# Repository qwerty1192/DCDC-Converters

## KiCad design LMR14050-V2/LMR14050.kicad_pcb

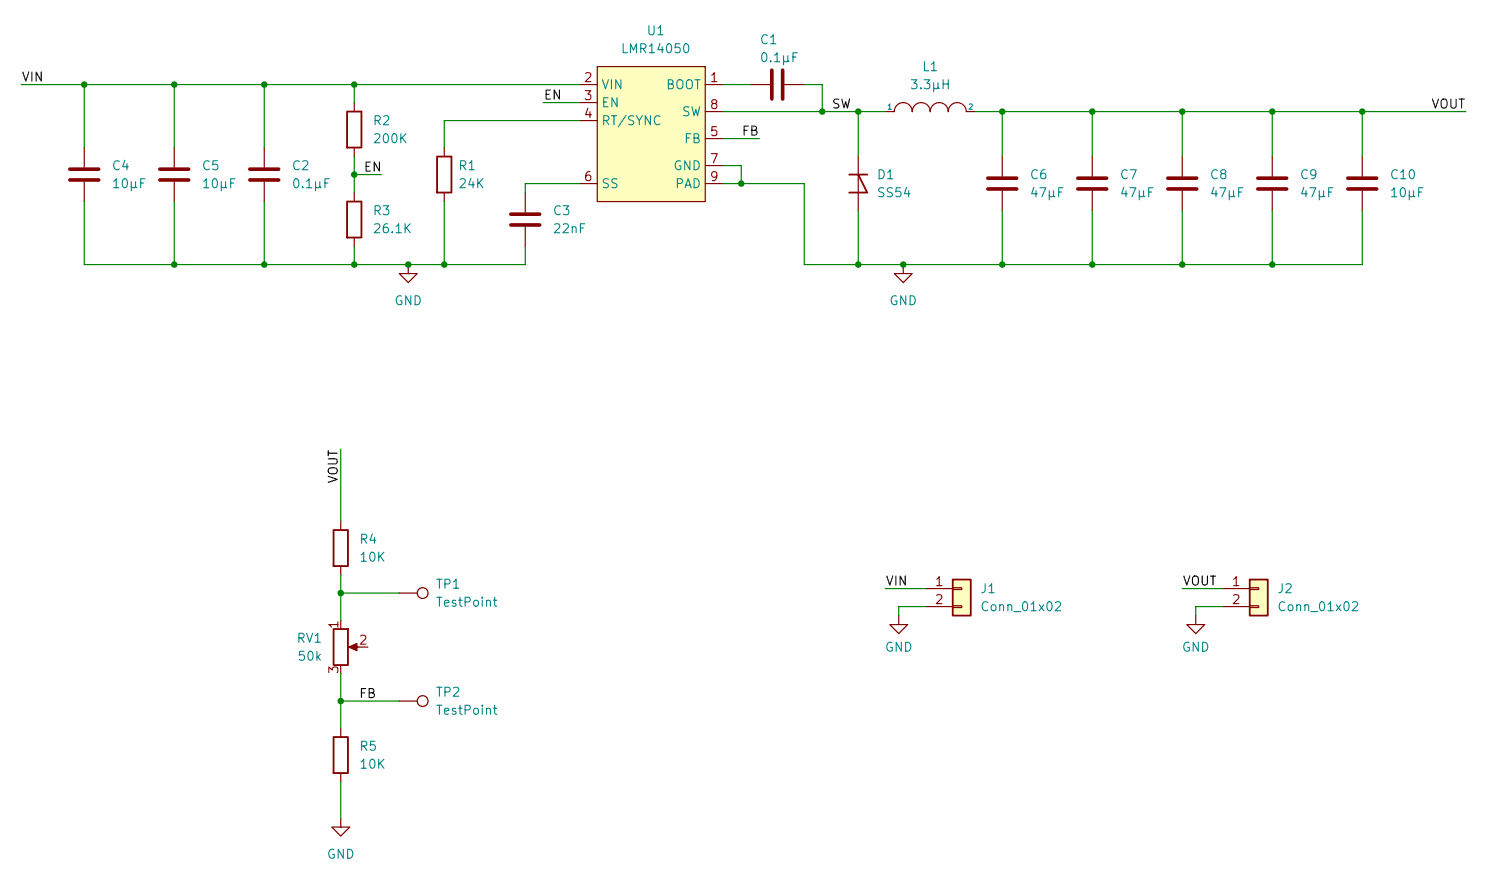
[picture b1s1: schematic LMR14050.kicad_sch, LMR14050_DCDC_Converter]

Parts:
C1, C2: 0.1µF; C_0603_1608Metric
C3: 22nF; C_0603_1608Metric
C4, C5: 10µF; C_1210_3225Metric
C6, C7, C8, C9: 47µF; C_1206_3216Metric
C10: 10µF; C_0603_1608Metric
D1: SS54; D_SMA
J1, J2: Conn_01x02; JST_XH_S2B-XH-A_1x02_P2.50mm_Horizontal
L1: 3.3µH; FX06x0
R1: 24K; R_0603_1608Metric
R2: 200K; R_0603_1608Metric
R3: 26.1K; R_0603_1608Metric
R4, R5: 10K; R_0603_1608Metric
RV1: 50k; G32A
TP1, TP2: TestPoint; TestPoint_Pad_D1.5mm
U1: LMR14050; HSOP-8-1EP_3.9x4.9mm_P1.27mm_EP2.41x3.1mm

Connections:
/EN: R2.2, R3.1, U1.3 (EN)
/FB: R5.1, RV1.3, TP2.1, U1.5 (FB)
/SW: C1.2, D1.1 (K), L1.1, U1.8 (SW)
/VIN: C2.1, C4.1, C5.1, J1.1, R2.1, U1.2 (VIN)
/VOUT: C6.1, C7.1, C8.1, C9.1, C10.1, J2.1, L1.2, R4.1
GND: C2.2, C3.2, C4.2, C5.2, C6.2, C7.2, C8.2, C9.2, C10.2, D1.2 (A), J1.2, J2.2, R1.2, R3.2, R5.2, U1.7 (GND), U1.9 (PAD)
unnamed: R4.2, RV1.1, TP1.1
unnamed: C1.1, U1.1 (BOOT)
unnamed: R1.1, U1.4 (RT/SYNC)
unnamed: C3.1, U1.6 (SS)

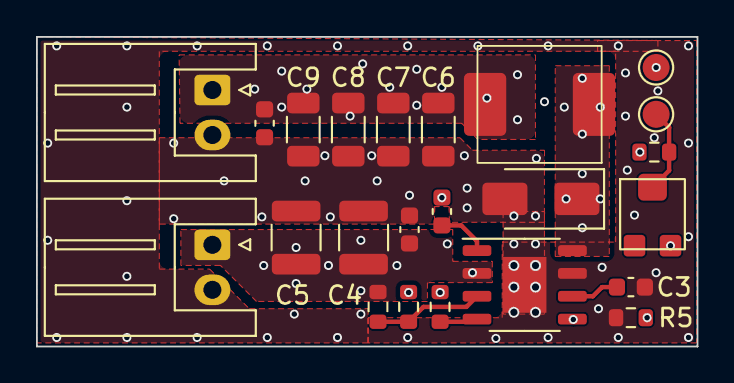
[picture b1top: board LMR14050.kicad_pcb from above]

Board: 6 copper layers, 36.7 x 17.2 mm, 23 parts (0 on the bottom side), 10 nets.

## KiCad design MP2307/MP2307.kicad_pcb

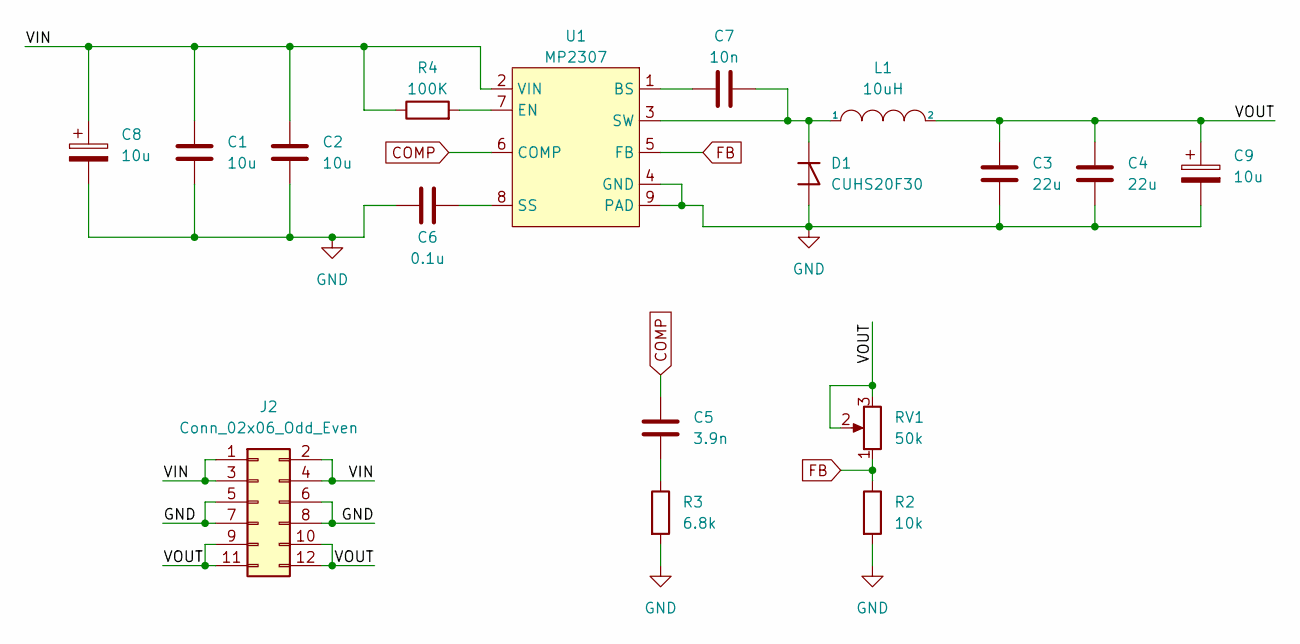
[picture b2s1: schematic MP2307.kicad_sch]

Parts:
C1, C2: 10u; C_0805_2012Metric_Pad1.18x1.45mm_HandSolder
C3, C4: 22u; C_0805_2012Metric_Pad1.18x1.45mm_HandSolder
C5: 3.9n; C_0603_1608Metric_Pad1.08x0.95mm_HandSolder
C6: 0.1u; C_0402_1005Metric
C7: 10n; C_0402_1005Metric
C8, C9: 10u; CP_Radial_D6.3mm_P2.50mm
D1: CUHS20F30; D_TUMD2
J2: Conn_02x06_Odd_Even; PinHeader_2x06_P2.54mm_Vertical
L1: 10uH; Inductor_KOHERelec_MDA7030
R2: 10k; R_0402_1005Metric
R3: 6.8k; R_0603_1608Metric
R4: 100K; R_0402_1005Metric
RV1: 50k; PVZ3A_variable_resistor
U1: MP2307; SOIC-8-1EP_3.9x4.9mm_P1.27mm_EP2.62x3.51mm_ThermalVias

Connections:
/VIN: C1.1, C2.1, C8.1, J2.1, J2.2, J2.3, J2.4, R4.1, U1.2 (VIN)
/VOUT: C3.1, C4.1, C9.1, J2.9, J2.10, J2.11, J2.12, L1.2, RV1.2, RV1.3
COMP: C5.1, U1.6 (COMP)
FB: R2.1, RV1.1, U1.5 (FB)
GND: C1.2, C2.2, C3.2, C4.2, C6.1, C8.2, C9.2, D1.2 (A), J2.5, J2.6, J2.7, J2.8, R2.2, R3.2, U1.4 (GND), U1.9 (PAD)
unnamed: C5.2, R3.1
unnamed: C7.2, D1.1 (K), L1.1, U1.3 (SW)
unnamed: C7.1, U1.1 (BS)
unnamed: R4.2, U1.7 (EN)
unnamed: C6.2, U1.8 (SS)

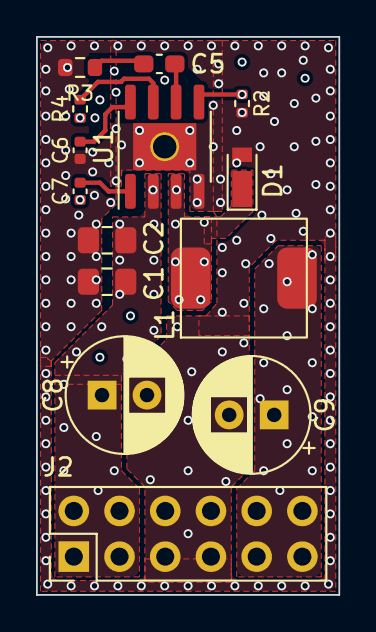
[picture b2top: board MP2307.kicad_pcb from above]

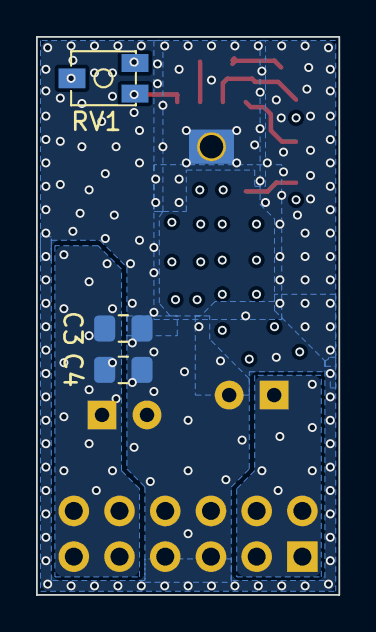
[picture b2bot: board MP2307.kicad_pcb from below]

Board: 6 copper layers, 16.8 x 31.0 mm, 17 parts (3 on the bottom side), 10 nets.

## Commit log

2024-10-02 licence
2024-10-02 gitignore
2024-10-02 MP2307
2024-10-02 LM14050
2024-10-02 LM14050-ver2
